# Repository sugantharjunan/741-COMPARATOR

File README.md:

# 741 Comparator Circuit – KiCad PCB Design

A simple and compact **741 Comparator Circuit** designed using **KiCad EDA** for schematic capture and PCB layout. This project uses the **LM741 operational amplifier** as a voltage comparator with an **NTC thermistor** for temperature-based detection and LED indication.

The circuit demonstrates analog signal comparison and threshold detection, making it suitable for learning operational amplifiers, sensor interfacing, and PCB design.

---

# Project Overview

This project demonstrates:

* Comparator circuit using LM741
* Temperature sensing using NTC thermistor
* PCB design in KiCad
* Analog voltage comparison
* LED status indication
* Through-hole component layout
* 3D PCB visualization

---

# Features

* LM741-based comparator circuit
* Temperature sensing using NTC
* LED output indication
* Compact PCB design
* Through-hole components
* Beginner-friendly analog electronics project
* Designed using KiCad

---

# Software Used

* KiCad

Official Website: [KiCad Official Website](https://www.kicad.org?utm_source=chatgpt.com)

---

# Hardware Components

| Component       | Description               |
| --------------- | ------------------------- |
| LM741           | Operational Amplifier     |
| NTC Thermistor  | Temperature Sensor        |
| LED             | Output Indicator          |
| Resistors       | Voltage Divider & Biasing |
| DIP Socket      | IC Mounting               |
| Power Connector | DC Input                  |

---

# Project Structure

```bash id="7t2z0l"
741-COMPARATOR/
│
├── Schematic/
│   └── 741_comparator.kicad_sch
│
├── PCB/
│   └── 741_comparator.kicad_pcb
│
├── Gerber/
│   └── Manufacturing_Files
│
├── Images/
│   ├── 741_3D_FRONT.png
│   ├── 741_3D_BACK.png
│   ├── 741_PCB.png
│   └── 741_SCHEMATIC.png
│
└── README.md
```

---

# Circuit Description

The circuit uses the **LM741 operational amplifier** in comparator mode.

An NTC thermistor changes resistance based on temperature. The op-amp compares the thermistor voltage with a reference voltage generated by resistor dividers.

When the input voltage crosses the threshold:

* The comparator output changes state
* The LED turns ON or OFF

---

# Working Principle

1. The NTC thermistor senses temperature changes.
2. Resistance of the thermistor varies with temperature.
3. Voltage divider generates varying input voltage.
4. LM741 compares:

   * Reference voltage
   * Sensor voltage
5. Output changes depending on comparison result.
6. LED indicates comparator output status.

---

# PCB Design

The PCB was designed with:

* Compact analog signal routing
* Proper spacing between components
* Through-hole assembly
* Easy soldering access
* Clean single-layer routing

---

# Electrical Specifications

| Parameter         | Value          |
| ----------------- | -------------- |
| Operating Voltage | 12V DC         |
| Comparator IC     | LM741          |
| Sensor Type       | NTC Thermistor |
| Output Type       | LED Indicator  |
| PCB Tool          | KiCad          |

---

# Applications

* Temperature Detection
* Threshold Monitoring
* Analog Electronics Learning
* Sensor Interfacing
* Comparator Circuit Practice
* Embedded Hardware Prototyping

---

# Circuit Behavior

* Low temperature → Comparator output changes state
* High temperature → LED indication changes

Threshold depends on:

* Thermistor value
* Resistor divider network

---

# Future Improvements

* Add adjustable threshold potentiometer
* Add buzzer output
* Add relay control
* Add digital display
* Convert to LM358/LM393 for single-supply optimization

---

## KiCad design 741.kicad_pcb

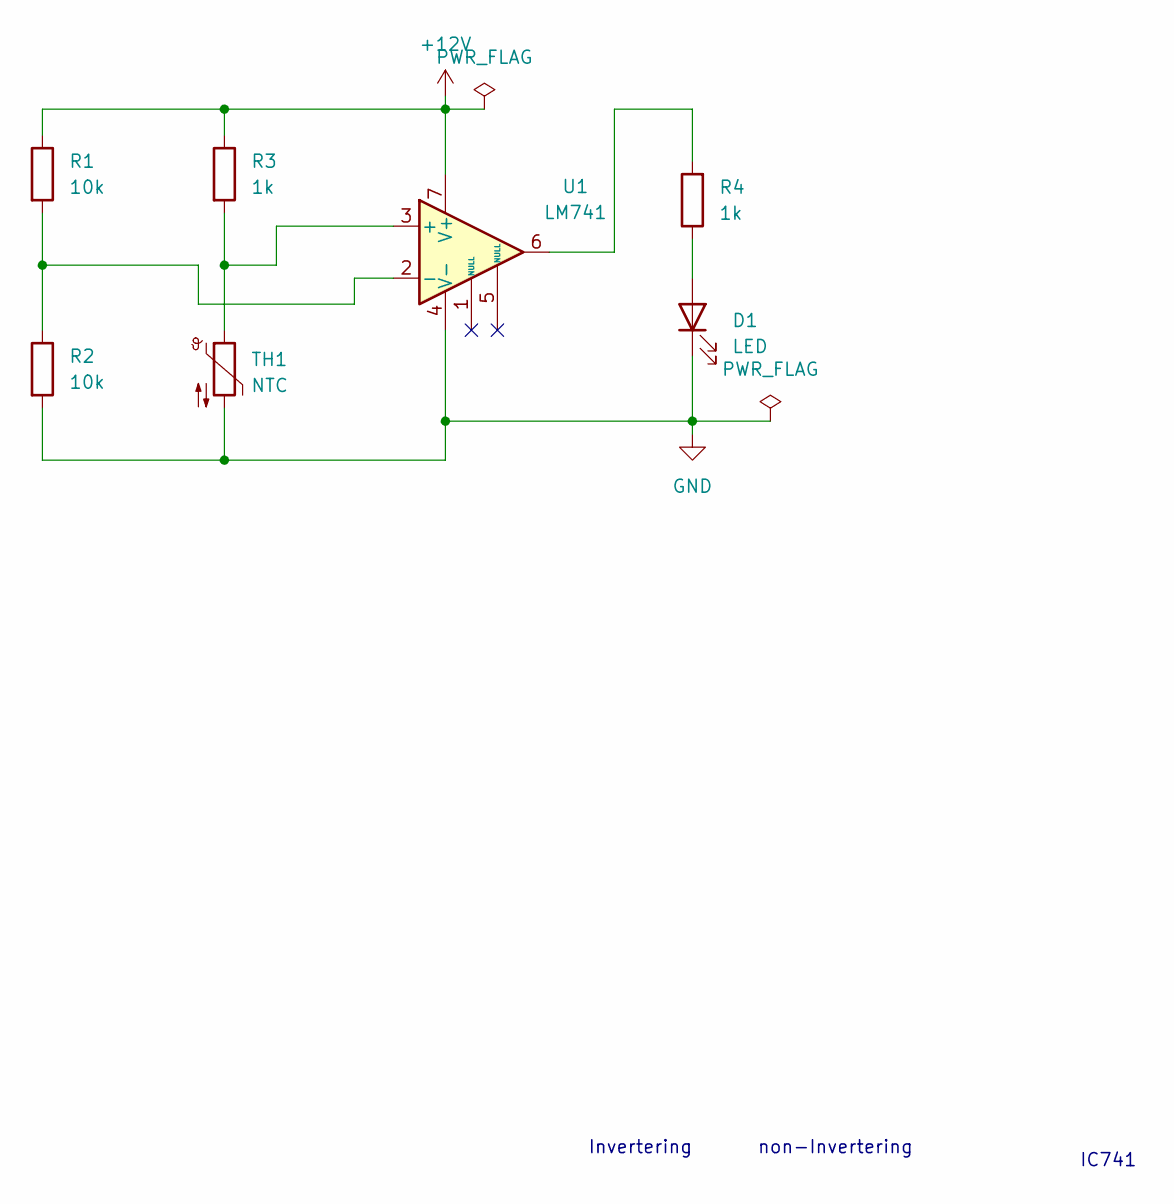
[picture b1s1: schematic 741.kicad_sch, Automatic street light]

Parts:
D1: LED; LED_D3.0mm_Clear
R1, R2: 10k; R_Axial_DIN0207_L6.3mm_D2.5mm_P7.62mm_Horizontal
R3, R4: 1k; R_Axial_DIN0207_L6.3mm_D2.5mm_P7.62mm_Horizontal
TH1: NTC; Heraeus_TO-92-2
U1: LM741; DIP-8_W7.62mm_Socket

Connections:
+12V: R1.1, R3.1, U1.7 (V+)
GND: D1.1 (K), R2.2, TH1.2, U1.4 (V-)
unnamed: D1.2 (A), R4.1
unnamed: R4.2, U1.6
unnamed: R3.2, TH1.1, U1.3 (+)
unnamed: R1.2, R2.1, U1.2 (-)

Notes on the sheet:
non-Invertering
IC741
Invertering

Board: 2 copper layers, 7 parts (0 on the bottom side), 6 nets, no tracks yet.
